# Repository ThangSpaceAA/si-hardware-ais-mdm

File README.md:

# si-hardware-ais-mdm
phần cứng module AIS

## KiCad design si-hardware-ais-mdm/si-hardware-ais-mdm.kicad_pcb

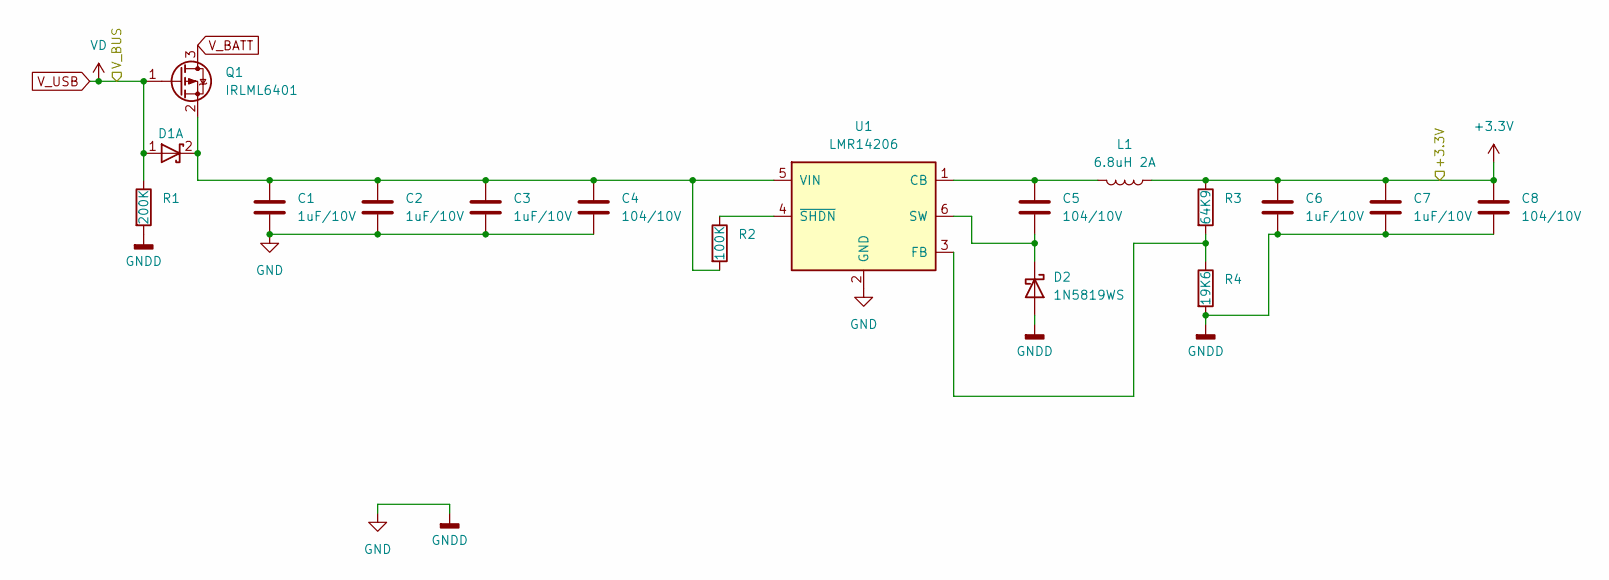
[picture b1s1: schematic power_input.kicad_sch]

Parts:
C1, C2, C3, C6, C7: 1uF/10V; C_0603_1608Metric
C4, C5, C8: 104/10V; C_0603_1608Metric
D1: 10V 2A; D_SOD-123
D2: 1N5819WS; D_SOD-323_HandSoldering
L1: 6.8uH 2A; Inductor_4.7x4.7mm_H3.0mm
Q1: IRLML6401; SOT-23
R1: 200K; C_0402_1005Metric
R2: 100K; C_0402_1005Metric
R3: 64K9; C_0402_1005Metric
R4: 19K6; C_0402_1005Metric
U1: LMR14206; SOT-23-6

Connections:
+3.3V: C6.1, C7.1, C8.1, L1.1, R3.1; also elsewhere on the board
unnamed: C1.1, C2.1, C3.1, C4.1, D1.2 (K), Q1.2 (S), R2.2, U1.5 (VIN)
unnamed: C5.2, D2.1 (K), U1.6 (SW)
unnamed: C5.1, L1.2, U1.1 (CB)
unnamed: R3.2, R4.1, U1.3 (FB)
unnamed: R2.1, U1.4 (~SHDN)
V_BATT: Q1.3 (D)
V_USB: D1.1 (A), Q1.1 (G), R1.1; also elsewhere on the board
bat-: C1.2, C2.2, C3.2, C4.2, C6.2, C7.2, C8.2, D2.2 (A), R1.2, R4.2, U1.2 (GND); also elsewhere on the board

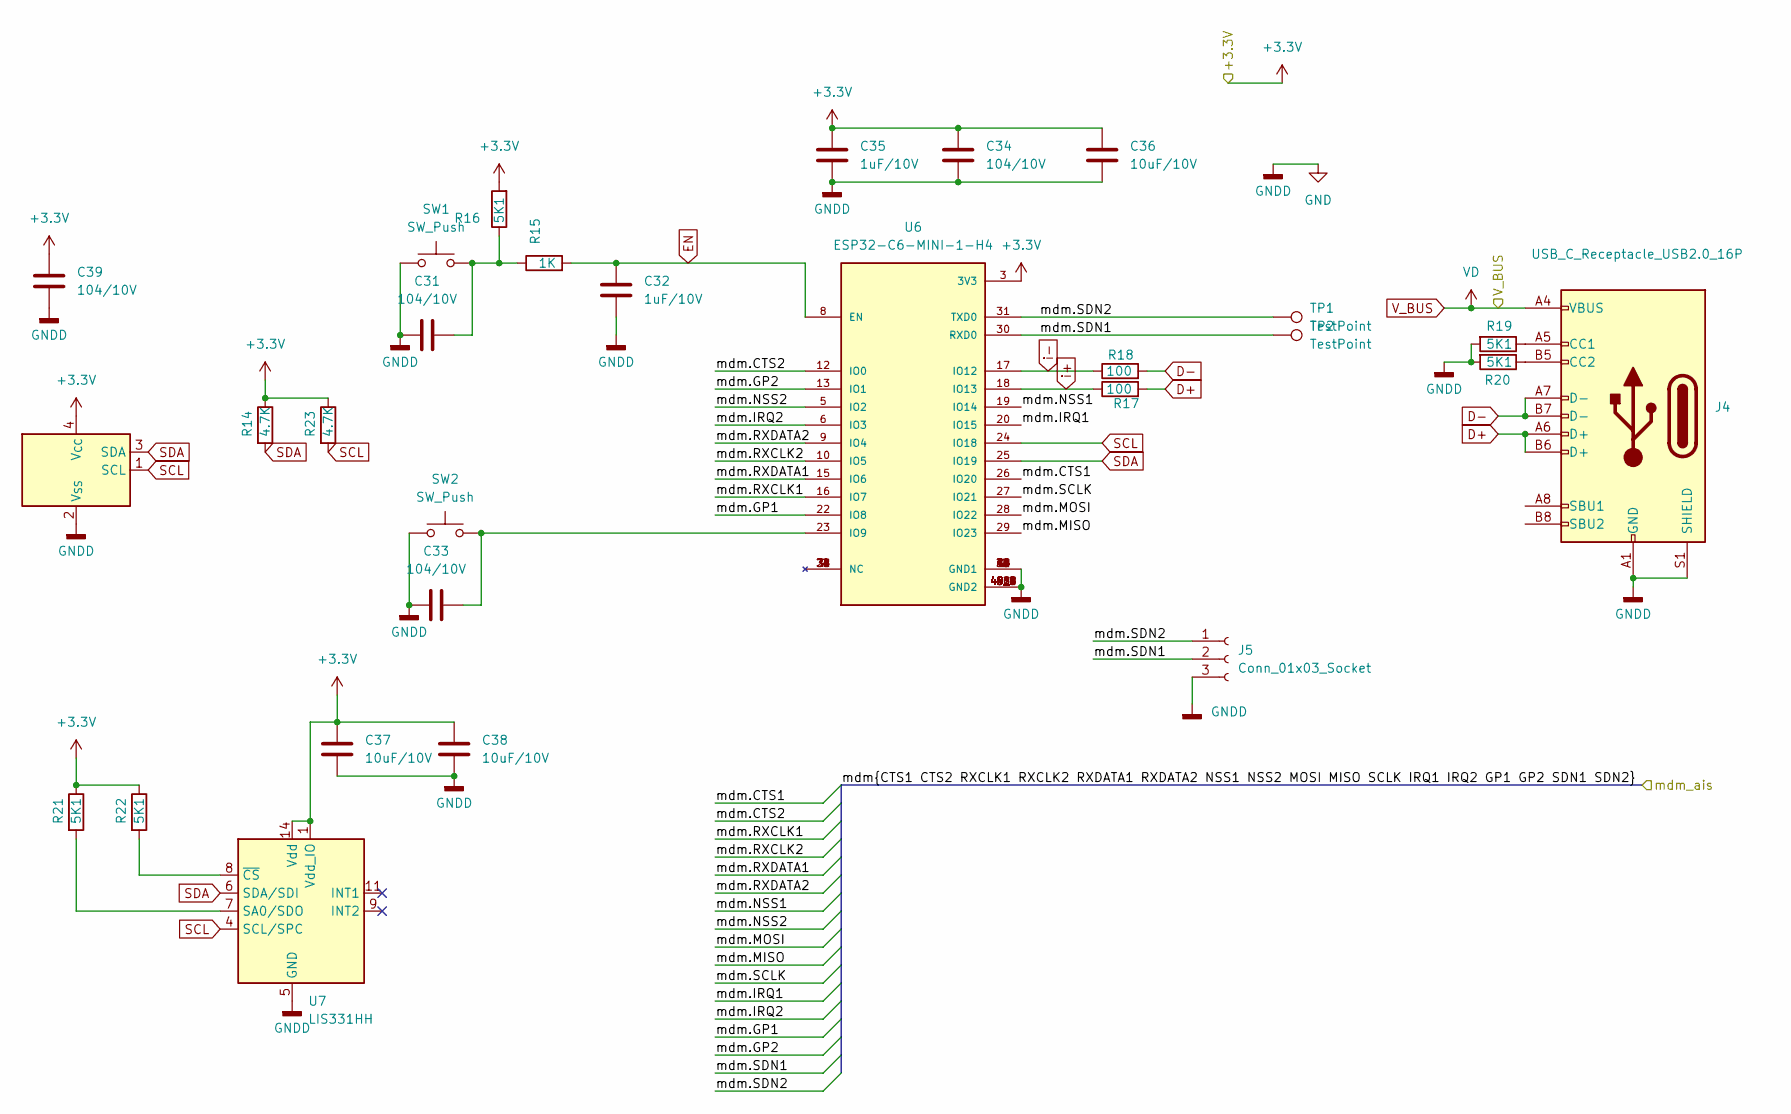
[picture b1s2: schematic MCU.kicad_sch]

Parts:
C31, C33, C39: 104/10V; C_0402_1005Metric
C32, C35: 1uF/10V; C_0603_1608Metric
C34: 104/10V; C_0603_1608Metric
C36, C37, C38: 10uF/10V; C_0603_1608Metric
J4: USB_C_Receptacle_USB2.0_16P; USB_C_Receptacle_G-Switch_GT-USB-7010ASV
J5: Conn_01x03_Socket; PinHeader_1x03_P2.54mm_Horizontal
R14, R23: 4.7K; R_0402_1005Metric
R15: 1K; R_0402_1005Metric
R16, R19, R20, R21, R22: 5K1; R_0402_1005Metric
R17, R18: 100; R_0402_1005Metric
SW1, SW2: SW_Push; SW_Tactile_SPST_NO_Straight_CK_PTS636Sx25SMTRLFS
TP1, TP2: TestPoint; TestPoint_Pad_D1.0mm
U6: ESP32-C6-MINI-1-H4; XCVR_ESP32-C6-MINI-1-H4; PARTREV 1.0
U7: LIS331HH; LGA-16_3x3mm_P0.5mm_LayoutBorder3x5y
U9: 24AA02E-OT; SOT-23-5

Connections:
+3.3V: C34.2, C35.2, C36.2, C37.2, C38.2, C39.1, R14.1, R16.2, R21.1, R22.1, R23.1, U6.3 (3V3), U7.1 (Vdd_IO), U7.14 (Vdd), U7.15 (Vdd), U9.4 (V_{CC}); also elsewhere on the board
/MCU/mdm.CTS1: U6.26 (IO20); also elsewhere on the board
/MCU/mdm.CTS2: U6.12 (IO0); also elsewhere on the board
/MCU/mdm.GP1: U6.22 (IO8); also elsewhere on the board
/MCU/mdm.GP2: U6.13 (IO1); also elsewhere on the board
/MCU/mdm.IRQ1: U6.20 (IO15); also elsewhere on the board
/MCU/mdm.IRQ2: U6.6 (IO3); also elsewhere on the board
/MCU/mdm.MISO: U6.29 (IO23); also elsewhere on the board
/MCU/mdm.MOSI: U6.28 (IO22); also elsewhere on the board
/MCU/mdm.NSS1: U6.19 (IO14); also elsewhere on the board
/MCU/mdm.NSS2: U6.5 (IO2); also elsewhere on the board
/MCU/mdm.RXCLK1: U6.16 (IO7); also elsewhere on the board
/MCU/mdm.RXCLK2: U6.10 (IO5); also elsewhere on the board
/MCU/mdm.RXDATA1: U6.15 (IO6); also elsewhere on the board
/MCU/mdm.RXDATA2: U6.9 (IO4); also elsewhere on the board
/MCU/mdm.SCLK: U6.27 (IO21); also elsewhere on the board
/MCU/mdm.SDN1: J5.2, TP2.1, U6.30 (RXD0); also elsewhere on the board
/MCU/mdm.SDN2: J5.1, TP1.1, U6.31 (TXD0); also elsewhere on the board
D+: J4.A6 (D+), J4.B6 (D+), R17.2
D-: J4.A7 (D-), J4.B7 (D-), R18.2
EN: C32.2, R15.2, U6.8 (EN)
unnamed: C31.1, R15.1, R16.1, SW1.2
unnamed: J4.A5 (CC1), R19.1
unnamed: J4.B5 (CC2), R20.1
unnamed: C33.1, SW2.2, U6.23 (IO9)
unnamed: R21.2, U7.7 (SA0/SDO)
unnamed: R22.2, U7.8 (~CS)
SCL: R23.2, U6.24 (IO18), U7.4 (SCL/SPC), U9.1 (SCL)
SDA: R14.2, U6.25 (IO19), U7.6 (SDA/SDI), U9.3 (SDA)
V_USB: J4.A4 (VBUS), J4.A9 (VBUS), J4.B4 (VBUS), J4.B9 (VBUS); also elsewhere on the board
bat-: C31.2, C32.1, C33.2, C34.1, C35.1, C36.1, C37.1, C38.1, C39.2, J4.A1 (GND), J4.A12 (GND), J4.B1 (GND), J4.B12 (GND), J4.S1 (SHIELD), J5.3, R19.2, R20.2, SW1.1, SW2.1, U6.1 (GND1), U6.2 (GND1), U6.11 (GND1), U6.14 (GND1), U6.36 (GND1), U6.37 (GND1), U6.38 (GND1), U6.39 (GND1), U6.40 (GND1), U6.41 (GND1), U6.42 (GND1), U6.43 (GND1), U6.44 (GND1), U6.45 (GND1), U6.46 (GND1), U6.47 (GND2), U6.48 (GND2), U6.49_1 (GND2), U6.49_2 (GND2), U6.49_3 (GND2), U6.49_4 (GND2), U6.49_5 (GND2), U6.49_6 (GND2), U6.49_7 (GND2), U6.49_8 (GND2), U6.49_9 (GND2), U6.50 (GND2), U6.51 (GND2), U6.52 (GND2), U6.53 (GND2), U7.5 (GND), U7.10 (GND), U7.12 (GND), U7.13 (GND), U7.16 (GND), U9.2 (V_{SS}); also elsewhere on the board
i+: R17.1, U6.18 (IO13)
i-: R18.1, U6.17 (IO12)

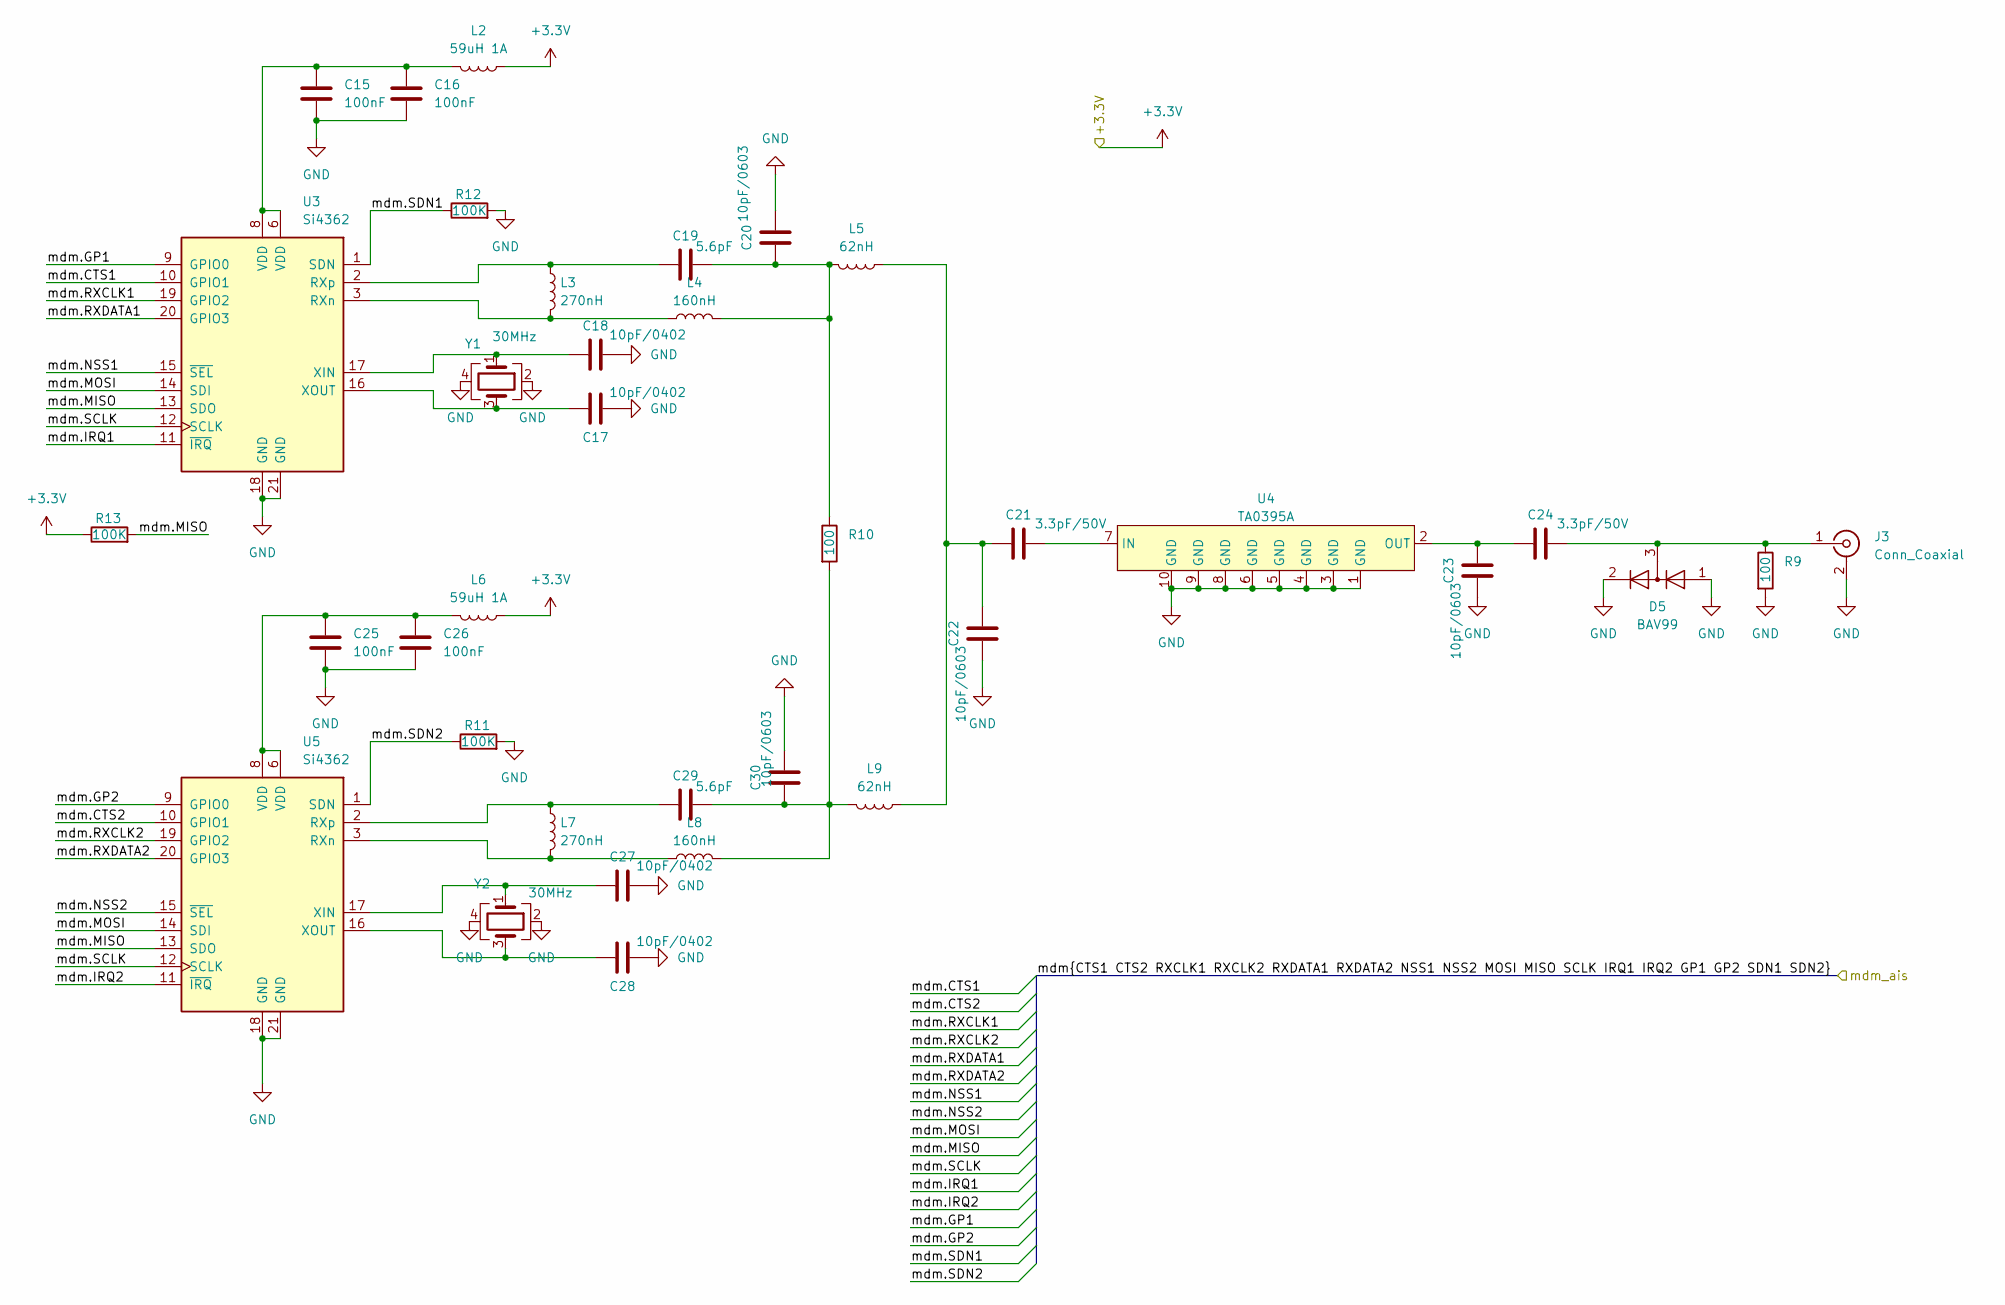
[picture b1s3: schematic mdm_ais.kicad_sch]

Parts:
C15, C16, C25, C26: 100nF; C_0402_1005Metric
C17, C18, C27, C28: 10pF/0402; C_0402_1005Metric
C19, C29: 5.6pF; C_0805_2012Metric
C20, C22, C23, C30: 10pF/0603; C_0603_1608Metric
C21, C24: 3.3pF/50V; C_0603_1608Metric
D5: BAV99; SOT-23
J3: Conn_Coaxial; SMA_Molex_73251-1153_EdgeMount_Horizontal
L2, L6: 59uH 1A; C_0402_1005Metric
L3, L7: 270nH; L_0603_1608Metric
L4, L8: 160nH; L_0603_1608Metric
L5, L9: 62nH; L_0603_1608Metric
R9, R10: 100; R_0603_1608Metric
R11, R12, R13: 100K; R_0603_1608Metric
U3, U5: Si4362; QFN-20-1EP_4x4mm_P0.5mm_EP2.5x2.5mm
U4: TA0395A
Y1, Y2: 30MHz; Crystal_SMD_SeikoEpson_TSX3225-4Pin_3.2x2.5mm

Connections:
+3.3V: L2.1, L6.1, R13.1; also elsewhere on the board
/MCU/mdm.CTS1: U3.10 (GPIO1); also elsewhere on the board
/MCU/mdm.CTS2: U5.10 (GPIO1); also elsewhere on the board
/MCU/mdm.GP1: U3.9 (GPIO0); also elsewhere on the board
/MCU/mdm.GP2: U5.9 (GPIO0); also elsewhere on the board
/MCU/mdm.IRQ1: U3.11 (~IRQ); also elsewhere on the board
/MCU/mdm.IRQ2: U5.11 (~IRQ); also elsewhere on the board
/MCU/mdm.MISO: R13.2, U3.13 (SDO), U5.13 (SDO); also elsewhere on the board
/MCU/mdm.MOSI: U3.14 (SDI), U5.14 (SDI); also elsewhere on the board
/MCU/mdm.NSS1: U3.15 (~SEL); also elsewhere on the board
/MCU/mdm.NSS2: U5.15 (~SEL); also elsewhere on the board
/MCU/mdm.RXCLK1: U3.19 (GPIO2); also elsewhere on the board
/MCU/mdm.RXCLK2: U5.19 (GPIO2); also elsewhere on the board
/MCU/mdm.RXDATA1: U3.20 (GPIO3); also elsewhere on the board
/MCU/mdm.RXDATA2: U5.20 (GPIO3); also elsewhere on the board
/MCU/mdm.SCLK: U3.12 (SCLK), U5.12 (SCLK); also elsewhere on the board
/MCU/mdm.SDN1: R12.1, U3.1 (SDN); also elsewhere on the board
/MCU/mdm.SDN2: R11.1, U5.1 (SDN); also elsewhere on the board
unnamed: C15.1, C16.1, L2.2, U3.6 (VDD), U3.8 (VDD)
unnamed: C19.1, C20.2, L4.2, L5.2, R10.1
unnamed: C21.2, C22.1, L5.1, L9.1
unnamed: C25.1, C26.1, L6.2, U5.6 (VDD), U5.8 (VDD)
unnamed: C29.1, C30.2, L8.2, L9.2, R10.2
unnamed: C24.1, D5.3 (K), J3.1 (In), R9.1
unnamed: L3.2, L4.1, U3.3 (RXn)
unnamed: C19.2, L3.1, U3.2 (RXp)
unnamed: C18.2, U3.17 (XIN), Y1.1
unnamed: C17.1, U3.16 (XOUT), Y1.3
unnamed: C21.1, U4.7 (IN)
unnamed: C23.1, C24.2, U4.2 (OUT)
unnamed: L7.2, L8.1, U5.3 (RXn)
unnamed: C29.2, L7.1, U5.2 (RXp)
unnamed: C27.2, U5.17 (XIN), Y2.1
unnamed: C28.1, U5.16 (XOUT), Y2.3
bat-: C15.2, C16.2, C17.2, C18.1, C20.1, C22.2, C23.2, C25.2, C26.2, C27.1, C28.2, C30.1, D5.1 (K), D5.2 (A), J3.2 (Ext), R9.2, R11.2, R12.2, U3.18 (GND), U3.21 (GND), U4.1 (GND), U4.3 (GND), U4.4 (GND), U4.5 (GND), U4.6 (GND), U4.8 (GND), U4.9 (GND), U4.10 (GND), U5.18 (GND), U5.21 (GND), Y1.2, Y1.4, Y2.2, Y2.4; also elsewhere on the board

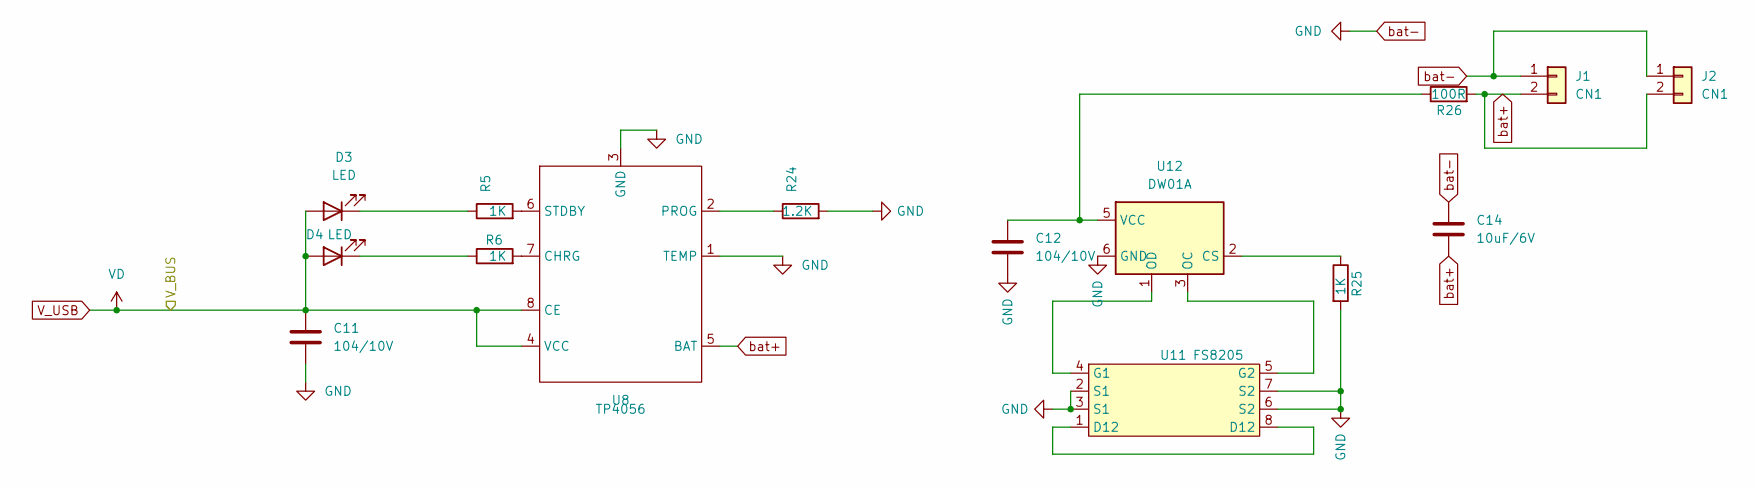
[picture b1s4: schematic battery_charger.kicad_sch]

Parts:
C11, C12: 104/10V; C_0603_1608Metric
C14: 10uF/6V; C_0603_1608Metric
D3, D4: LED; LED_0805_2012Metric
J1, J2: CN1; Stocko_MKS_1652-6-0-202_1x2_P2.50mm_Vertical
R5, R6, R25: 1K; R_0603_1608Metric
R24: 1.2K; R_0603_1608Metric
R26: 100R; R_0603_1608Metric
U8: TP4056; SOP-8_3.9x4.9mm_P1.27mm
U11: FS8205; TSSOP-8_4.4x3mm_P0.65mm
U12: DW01A; SOT-23-6

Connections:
unnamed: D3.1 (K), R5.1
unnamed: D4.1 (K), R6.1
unnamed: R6.2, U8.7 (CHRG)
unnamed: R24.1, U8.2 (PROG)
unnamed: R5.2, U8.6 (STDBY)
unnamed: U11.1 (D12), U11.8 (D12)
unnamed: U11.4 (G1), U12.1 (OD)
unnamed: U11.5 (G2), U12.3 (OC)
unnamed: R25.1, U12.2 (CS)
unnamed: C12.2, R26.1, U12.5 (VCC)
V_USB: C11.2, D3.2 (A), D4.2 (A), U8.4 (VCC), U8.8 (CE); also elsewhere on the board
bat+: C14.1, J1.2, J2.2, R26.2, U8.5 (BAT)
bat-: C11.1, C12.1, C14.2, J1.1, J2.1, R24.2, R25.2, U8.1 (TEMP), U8.3 (GND), U11.2 (S1), U11.3 (S1), U11.6 (S2), U11.7 (S2), U12.6 (GND); also elsewhere on the board

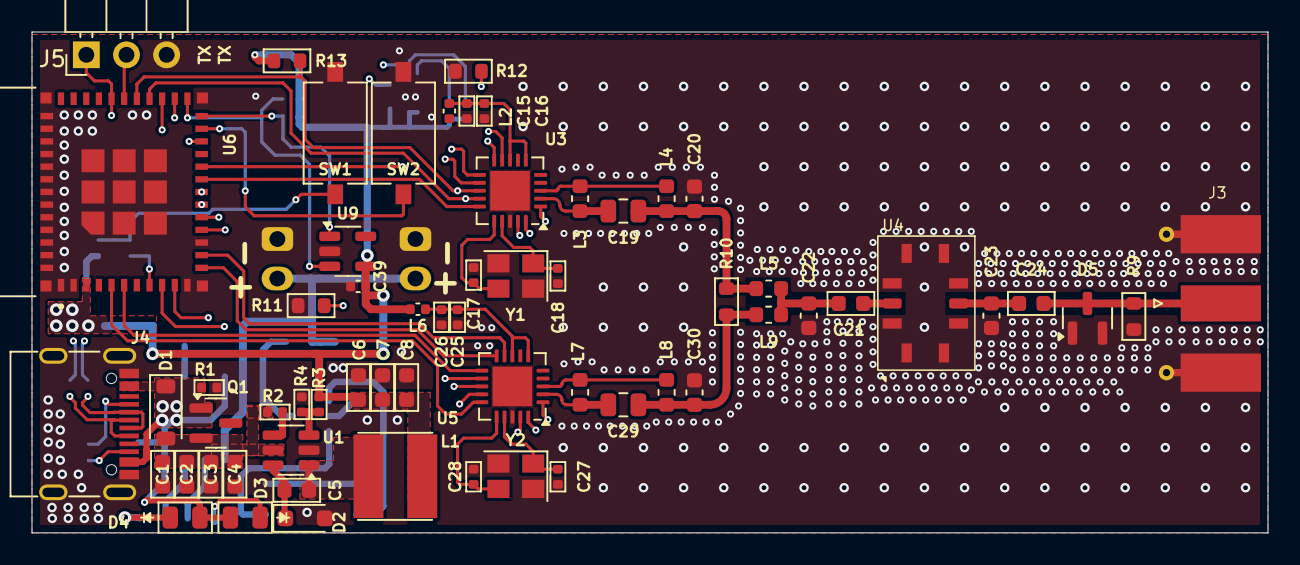
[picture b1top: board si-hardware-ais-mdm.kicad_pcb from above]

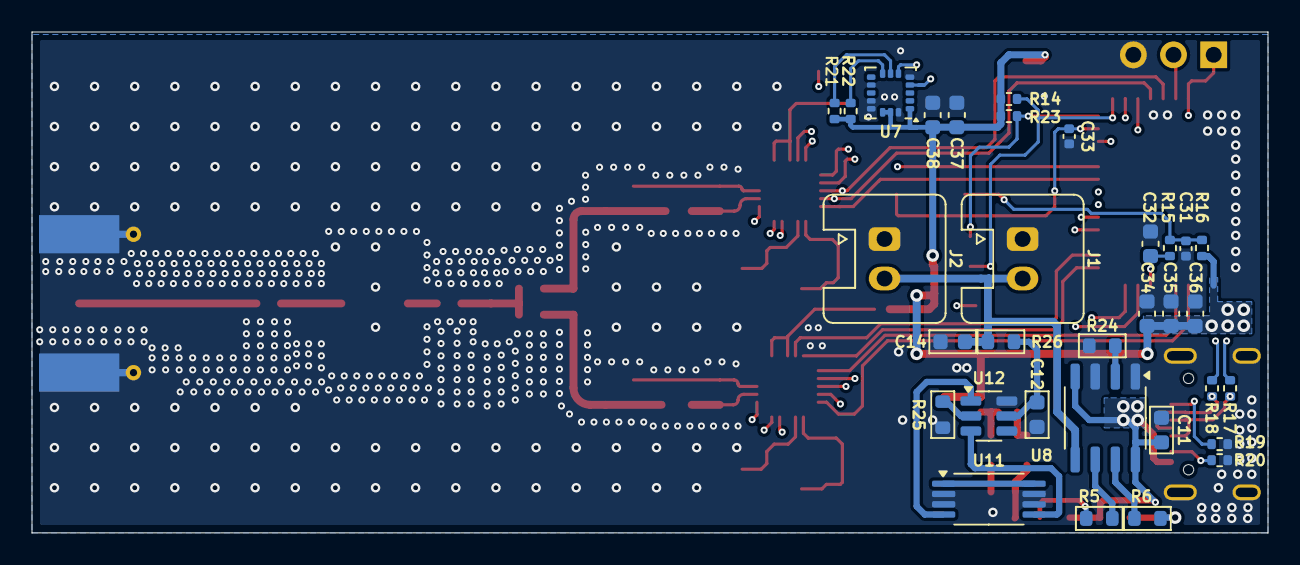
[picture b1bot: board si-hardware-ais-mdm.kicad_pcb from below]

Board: 4 copper layers, 78.2 x 31.7 mm, 94 parts (32 on the bottom side), 65 nets.

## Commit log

2025-08-29 add file requriment
2025-09-05 power and charger mdm
2025-09-09 added function power input battery chargger mdm_ais
2025-09-15 added function MCU
2025-09-16 schematic to pcb
2025-09-17 scale board min length
2025-09-17 layout and routing
2025-09-18 routing 2
2025-09-18 routing 3
2025-09-18 routing 4
2025-09-23 added module flash
2025-09-24 added chip flash 24LC64
2025-09-27 added ic charger
2025-09-29 routing final
2025-10-03 added schematic pdf
2025-10-06 change mcu control
